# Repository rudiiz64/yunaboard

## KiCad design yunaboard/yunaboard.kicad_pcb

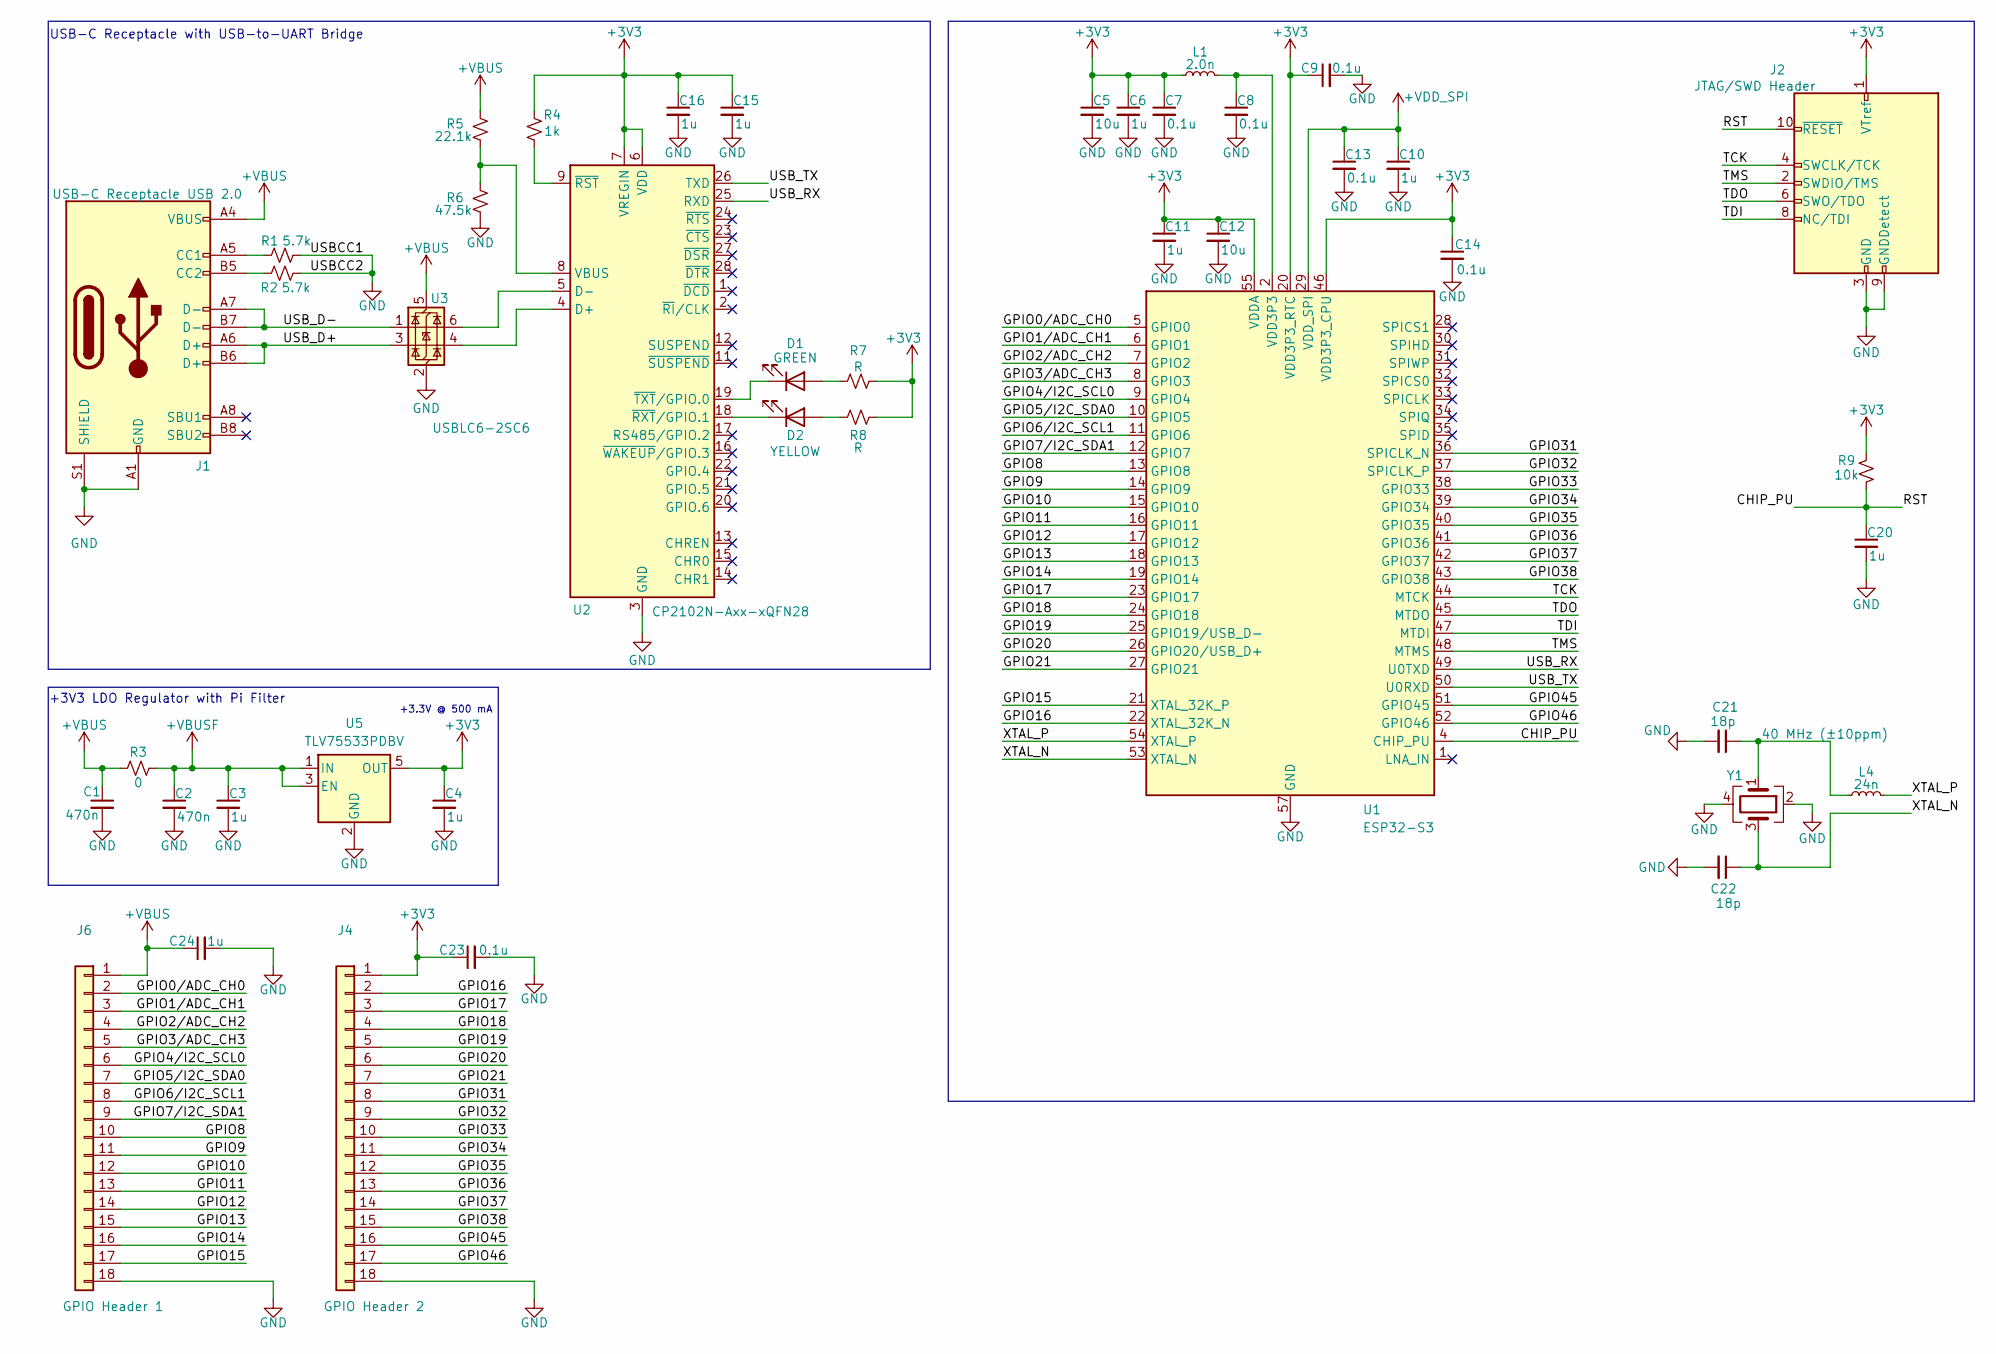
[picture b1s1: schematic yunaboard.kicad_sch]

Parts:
C1, C2: 470n; C_0603_1608Metric
C3, C4, C6, C10, C11, C15, C16, C20: 1u; C_0603_1608Metric
C5, C12: 10u; C_0603_1608Metric
C7, C8, C9, C13, C14, C23: 0.1u; C_0402_1005Metric
C21, C22: 18p; C_0402_1005Metric
C24: 1u; C_0402_1005Metric
D1: GREEN; LED_0603_1608Metric
D2: YELLOW; LED_0603_1608Metric
J1: USB-C Receptacle USB 2.0; USB_C_Receptacle_GCT_USB4105-xx-A_16P_TopMnt_Horizontal
J2: JTAG/SWD Header; PinHeader_2x06_P1.27mm_Vertical
J4: GPIO Header 2; PinHeader_1x18_P2.00mm_Vertical
J6: GPIO Header 1; PinHeader_1x18_P2.00mm_Vertical
L1: 2.0n; L_0201_0603Metric
L4: 24n; L_0201_0603Metric
R1, R2: 5.7k; R_0603_1608Metric
R3: 0; R_0402_1005Metric
R4: 1k; R_0402_1005Metric
R5: 22.1k; R_0402_1005Metric
R6: 47.5k; R_0402_1005Metric
R7, R8: R; R_0402_1005Metric
R9: 10k; R_0402_1005Metric
U1: ESP32-S3; QFN-56-1EP_7x7mm_P0.4mm_EP4x4mm
U2: CP2102N-Axx-xQFN28; QFN-28-1EP_5x5mm_P0.5mm_EP3.35x3.35mm
U3: USBLC6-2SC6; SOT-23-6
U5: TLV75533PDBV; SOT-23-5
Y1: 40 MHz (±10ppm); Crystal_SMD_3225-4Pin_3.2x2.5mm

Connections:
+3V3: C4.1, C5.1, C6.1, C7.1, C9.1, C11.1, C12.1, C14.1, C15.1, C16.1, C23.1, J2.1 (VTref), J4.1, L1.1, R4.1, R7.2, R8.2, R9.2, U1.20 (VDD3P3_RTC), U1.46 (VDD3P3_CPU), U1.55 (VDDA), U1.56 (VDDA), U2.6 (VDD), U2.7 (VREGIN), U5.5 (OUT)
+VBUS: C1.1, C24.1, J1.A4 (VBUS), J1.A9 (VBUS), J1.B4 (VBUS), J1.B9 (VBUS), J6.1, R3.2, R5.1, U3.5 (VBUS)
+VBUSF: C2.1, C3.1, R3.1, U5.1 (IN), U5.3 (EN)
+VDD_SPI: C10.1, C13.1, U1.29 (VDD_SPI)
/CHIP_PU: C20.1, J2.10 (~RESET), R9.1, U1.4 (CHIP_PU)
/GPIO0/ADC_CH0: J6.2, U1.5 (GPIO0)
/GPIO1/ADC_CH1: J6.3, U1.6 (GPIO1)
/GPIO2/ADC_CH2: J6.4, U1.7 (GPIO2)
/GPIO3/ADC_CH3: J6.5, U1.8 (GPIO3)
/GPIO4/I2C_SCL0: J6.6, U1.9 (GPIO4)
/GPIO5/I2C_SDA0: J6.7, U1.10 (GPIO5)
/GPIO6/I2C_SCL1: J6.8, U1.11 (GPIO6)
/GPIO7/I2C_SDA1: J6.9, U1.12 (GPIO7)
/GPIO8: J6.10, U1.13 (GPIO8)
/GPIO9: J6.11, U1.14 (GPIO9)
/GPIO10: J6.12, U1.15 (GPIO10)
/GPIO11: J6.13, U1.16 (GPIO11)
/GPIO12: J6.14, U1.17 (GPIO12)
/GPIO13: J6.15, U1.18 (GPIO13)
/GPIO14: J6.16, U1.19 (GPIO14)
/GPIO15: J6.17, U1.21 (XTAL_32K_P)
/GPIO16: J4.2, U1.22 (XTAL_32K_N)
/GPIO17: J4.3, U1.23 (GPIO17)
/GPIO18: J4.4, U1.24 (GPIO18)
/GPIO19: J4.5, U1.25 (GPIO19/USB_D-)
/GPIO20: J4.6, U1.26 (GPIO20/USB_D+)
/GPIO21: J4.7, U1.27 (GPIO21)
/GPIO31: J4.8, U1.36 (SPICLK_N)
/GPIO32: J4.9, U1.37 (SPICLK_P)
/GPIO33: J4.10, U1.38 (GPIO33)
/GPIO34: J4.11, U1.39 (GPIO34)
/GPIO35: J4.12, U1.40 (GPIO35)
/GPIO36: J4.13, U1.41 (GPIO36)
/GPIO37: J4.14, U1.42 (GPIO37)
/GPIO38: J4.15, U1.43 (GPIO38)
/GPIO45: J4.16, U1.51 (GPIO45)
/GPIO46: J4.17, U1.52 (GPIO46)
/TCK: J2.4 (SWCLK/TCK), U1.44 (MTCK)
/TDI: J2.8 (NC/TDI), U1.47 (MTDI)
/TDO: J2.6 (SWO/TDO), U1.45 (MTDO)
/TMS: J2.2 (SWDIO/TMS), U1.48 (MTMS)
/USB_D+: J1.A6 (D+), J1.B6 (D+), U3.3 (I/O2)
/USB_D-: J1.A7 (D-), J1.B7 (D-), U3.1 (I/O1)
/USB_RX: U1.49 (U0TXD), U2.25 (RXD)
/USB_TX: U1.50 (U0RXD), U2.26 (TXD)
/XTAL_N: C22.1, U1.53 (XTAL_N), Y1.3
/XTAL_P: L4.2, U1.54 (XTAL_P)
GND: C1.2, C2.2, C3.2, C4.2, C5.2, C6.2, C7.2, C8.2, C9.2, C10.2, C11.2, C12.2, C13.2, C14.2, C15.2, C16.2, C20.2, C21.2, C22.2, C23.2, C24.2, J1.A1 (GND), J1.A12 (GND), J1.B1 (GND), J1.B12 (GND), J1.S1 (SHIELD), J2.3 (GND), J2.5 (GND), J2.9 (GNDDetect), J4.18, J6.18, R1.1, R2.1, R6.2, U1.57 (GND), U2.3 (GND), U2.29 (GND), U3.2 (GND), U5.2 (GND), Y1.2, Y1.4
unnamed: C8.1, L1.2, U1.2 (VDD3P3), U1.3 (VDD3P3)
unnamed: C21.1, L4.1, Y1.1
unnamed: D1.2 (A), R7.1
unnamed: D1.1 (K), U2.19 (~TXT/GPIO.0)
unnamed: D2.2 (A), R8.1
unnamed: D2.1 (K), U2.18 (~RXT/GPIO.1)
unnamed: J1.A5 (CC1), R1.2
unnamed: J1.B5 (CC2), R2.2
unnamed: U2.4 (D+), U3.4 (I/O2)
unnamed: U2.5 (D-), U3.6 (I/O1)
unnamed: R5.2, R6.1, U2.8 (VBUS)
unnamed: R4.2, U2.9 (~RST)

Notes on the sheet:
+3V3 LDO Regulator with Pi Filter
USB-C Receptacle with USB-to-UART Bridge
+3.3V @ 500 mA

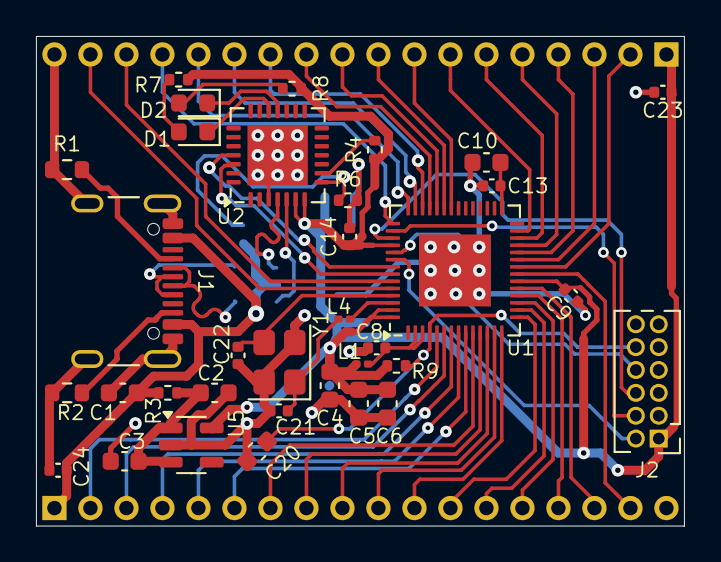
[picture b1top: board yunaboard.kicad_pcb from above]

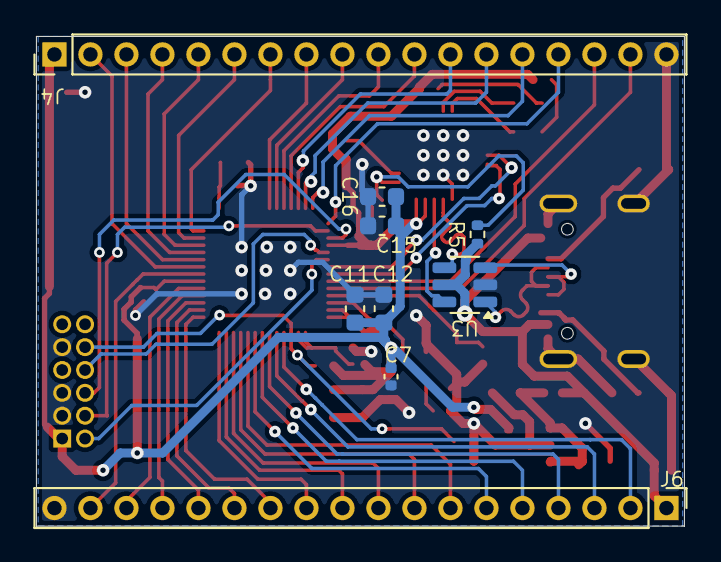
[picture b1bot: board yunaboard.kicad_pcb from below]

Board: 2 copper layers, 36.0 x 27.2 mm, 43 parts (9 on the bottom side), 60 nets.

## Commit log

2026-01-22 Rev 0.1
    - Created repo
    - Created project
    - Initial microcontroller ESP32-S3 placed
    - Initial USB-C Receptacle for 2.0 placed
    - Initial documentation for ESP32 and USB-C saved
2026-01-22 Rev 0.1
    - Added initial USB-C connections
    - Added ESD to USB-C data signals
    - Added initial USB-to-UART bridge IC
    - Added initial bulk capacitors to power inputs
    - Added initial +3.3V LDO regulator
    - Added initial ESP32 S3 circuitry
2026-01-26 Updated schematic
    - Placed JTAG tag connect
    - Placed initial circuitry to the ESP32 S3 (RF, chip PU)
    - Added some labels for better readability
    - Found some more documentation for the ESP32
    - Added some LEDs to the USB-to-UART bridge
2026-01-27 Updated
    - Added footprints to every component
    - Selected capacitors for the external crystals (TBT)
2026-01-28 Update
    - Added GPIO pin headers
    - Excluded RF antenna portion (LNA_IN) - may add in the future
    - Started initial PCB layout
2026-02-02 Update
    - Changed JTAG connector to pin header for SWD
    - Changed GPIO pin headers from 1mm length to 2mm length
    - Adjusted the layout of the PCB from the initial design
2026-02-03 Finalzed PCB
    - Changed LDO to TLV75533PDBVR for an output current of 500 mA
    - Adjusted some routing to reduce ground plane breaking
    - Adjusted some 3V3 traces to be 0.5mm instead of 0.3mm
2026-02-03 Updated reference sheets
    - Removed MIC LDO sheet and added TLV755P sheet
